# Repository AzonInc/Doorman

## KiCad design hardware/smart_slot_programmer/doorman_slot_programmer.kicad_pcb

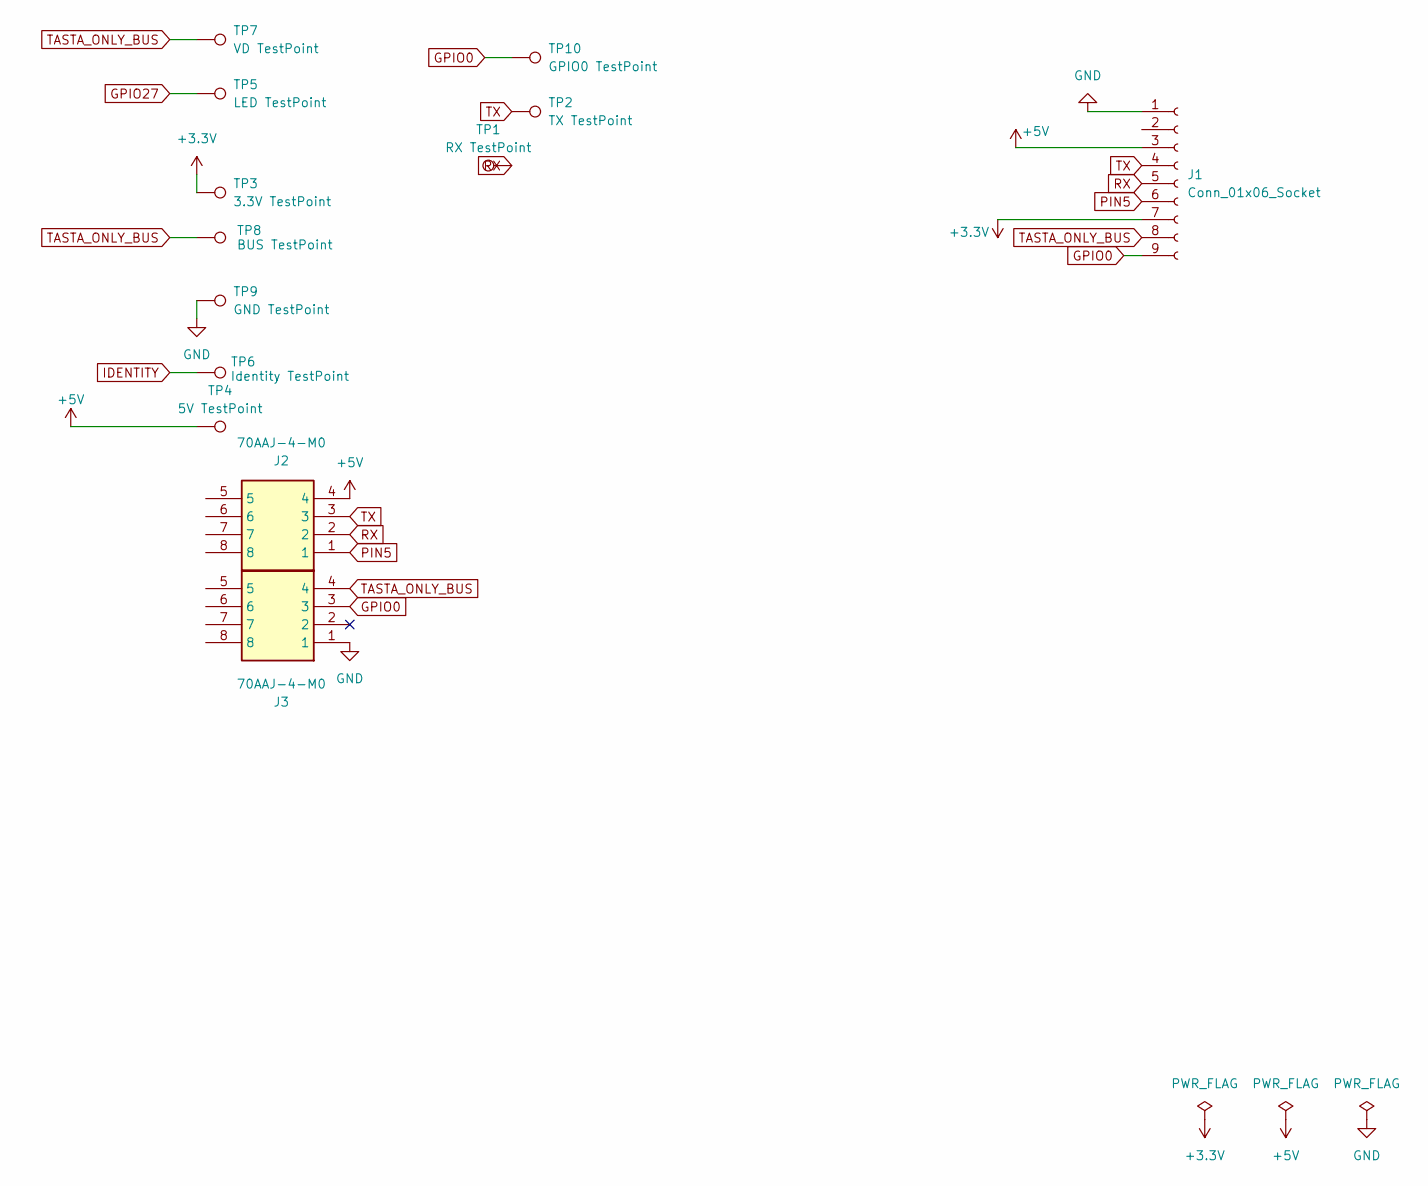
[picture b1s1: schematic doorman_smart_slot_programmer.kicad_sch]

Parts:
J1: Conn_01x06_Socket; PinSocket_1x09_P2.54mm_Horizontal
J2, J3: 70AAJ-4-M0; 70AAJ4M0; Manufacturer_Part_Number 70AAJ-4-M0; Mouser Part Number 652-70AAJ-4-M0
TP1: RX TestPoint; TestPoint_Pad_D1.0mm
TP2: TX TestPoint; TestPoint_Pad_D1.0mm
TP3: 3.3V TestPoint; TestPoint_Pad_D1.0mm
TP4: 5V TestPoint; TestPoint_Pad_D1.0mm
TP5: LED TestPoint; TestPoint_Pad_D1.0mm
TP6: Identity TestPoint; TestPoint_Pad_D1.0mm
TP7: VD TestPoint; TestPoint_Pad_D1.0mm
TP8: BUS TestPoint; TestPoint_Pad_D1.0mm
TP9: GND TestPoint; TestPoint_Pad_D1.0mm
TP10: GPIO0 TestPoint; TestPoint_Pad_D1.0mm

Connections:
+3.3V: J1.7, TP3.1
+5V: J1.3, J2.4, TP4.1
GND: J1.1, J3.1, TP9.1
GPIO0: J1.9, J3.3, TP10.1
GPIO27: TP5.1
IDENTITY: TP6.1
PIN5: J1.6, J2.1
RX: J1.5, J2.2, TP1.1
TASTA_ONLY_BUS: J1.8, J3.4, TP7.1, TP8.1
TX: J1.4, J2.3, TP2.1

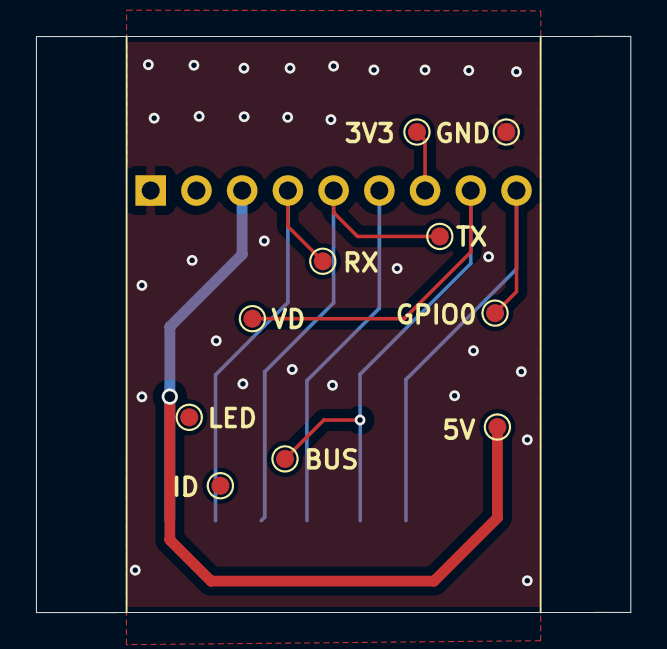
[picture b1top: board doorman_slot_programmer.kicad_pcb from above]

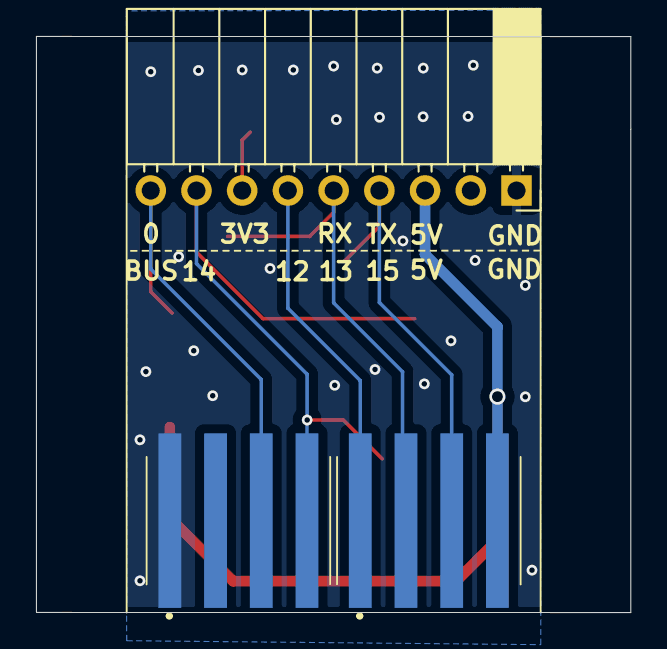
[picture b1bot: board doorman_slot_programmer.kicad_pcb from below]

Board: 4 copper layers, 33.0 x 32.0 mm, 13 parts (3 on the bottom side), 8 nets.

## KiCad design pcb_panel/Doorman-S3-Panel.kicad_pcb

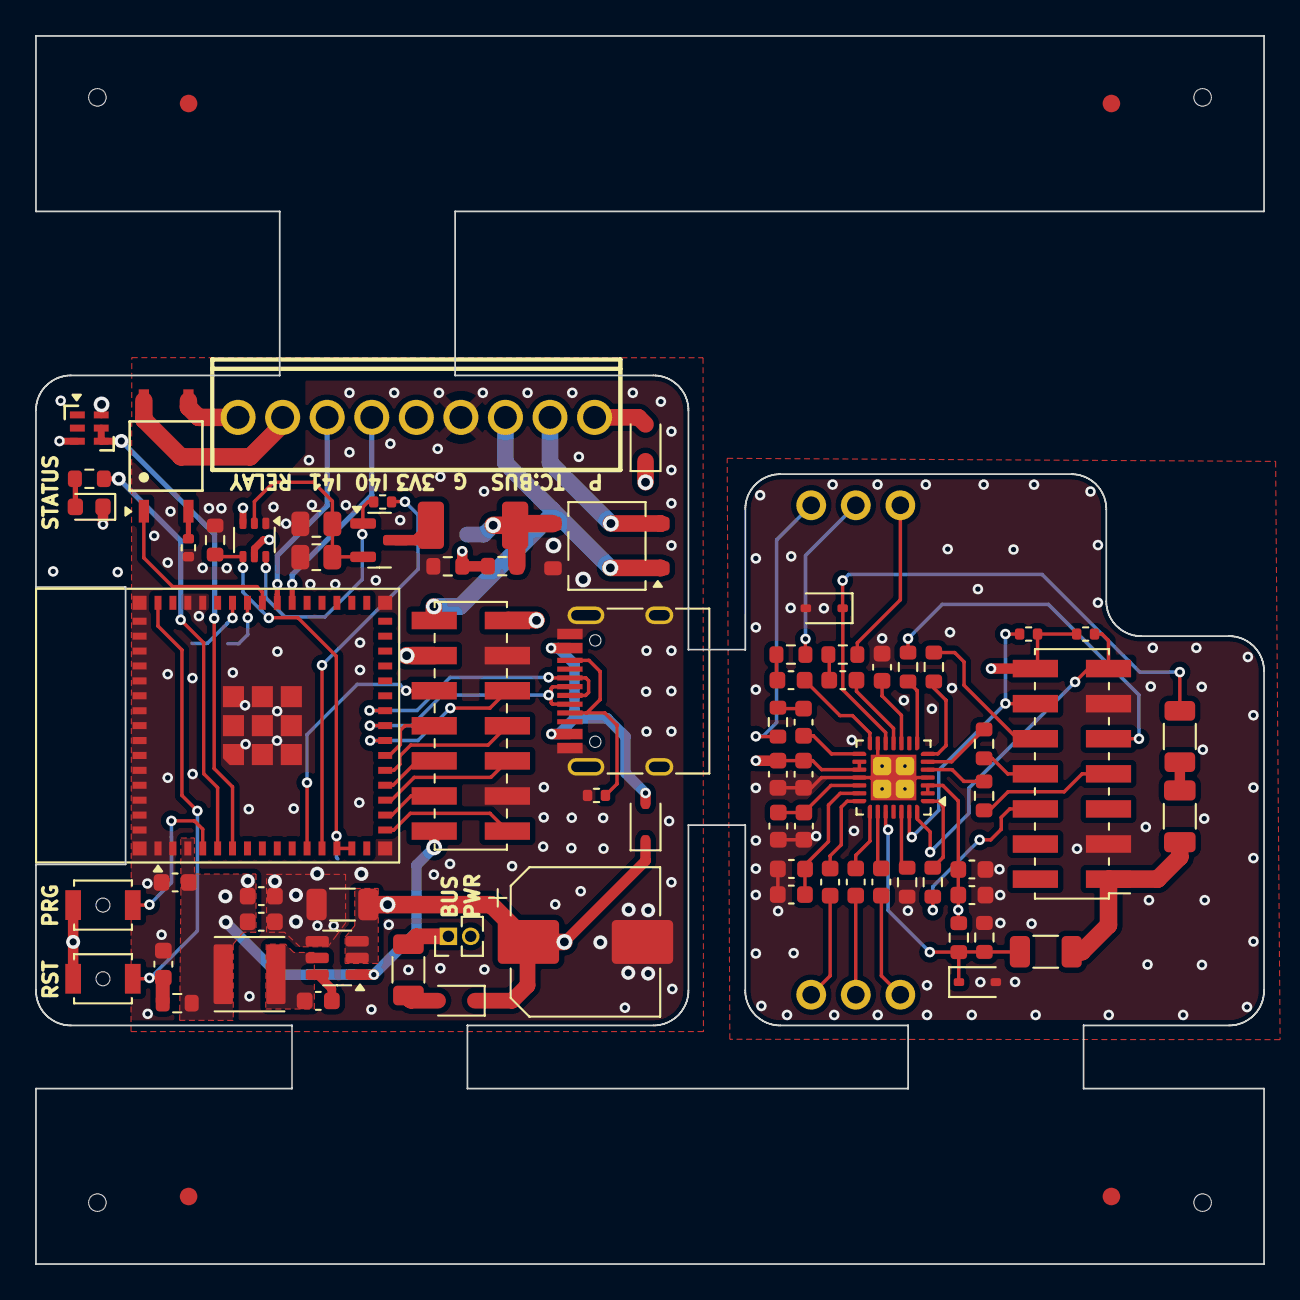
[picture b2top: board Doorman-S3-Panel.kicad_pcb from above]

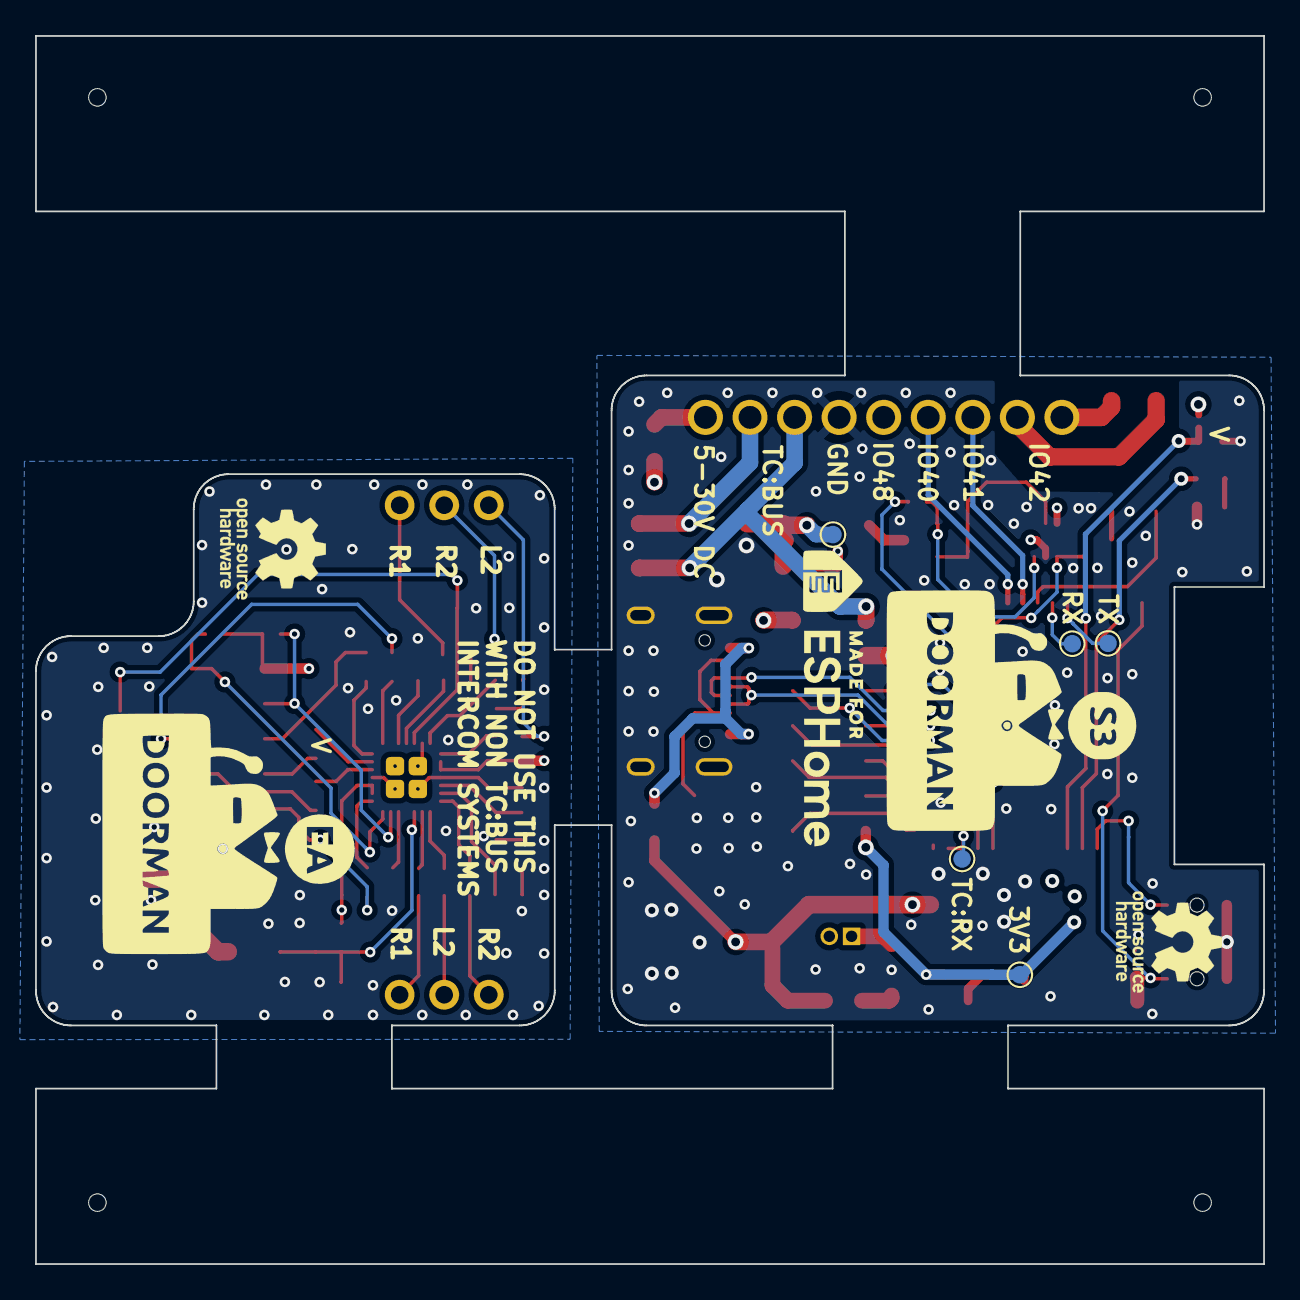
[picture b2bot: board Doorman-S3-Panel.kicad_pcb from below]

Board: 4 copper layers, 70.0 x 70.0 mm, 84 parts (12 on the bottom side), 79 nets.

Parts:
B0-C1, B0-C2, B0-C5, B1-C1, B1-C10, B1-C18, B1-C20: 100nF; C_0603_1608Metric
B0-C3: 470uF; CP_Elec_8x10
B0-C4: 10uF; C_1206_3216Metric
B0-C6, B0-C7: 22uF; C_0603_1608Metric
B0-D1, B0-D5, B0-D6: 1N5819WS; D_SOD-323
B0-D2: MB6S; TO-269AA
B0-D4: Red; LED_0603_1608Metric
B0-D7: 6.2V; D_MELF
B0-D8: XL-2020RGBC-SK6812B; LED-SMD_6P-L2.0-W2.0_XL-2020RGBC
B0-G***: LOGO; esphome
B0-G***#2, B1-G***: LOGO; doorman-s3-2
B0-J1: USB_C_Receptacle_USB2.0; USB_C_Receptacle_HRO_TYPE-C-31-M-12
B0-J2: Terminal; CONN-TH_9P-P2.54_KF128-2.54-9P
B0-J3: 3V3 Test Pad; TestPoint_Pad_D1.0mm
B0-J4: Conn_02x07_Odd_Even; PinSocket_2x07_P2.00mm_Vertical_SMD
B0-J6: BUS Test Pad; TestPoint_Pad_D1.0mm
B0-J7: BUS RX Test Pad; TestPoint_Pad_D1.0mm
B0-J8: TX Test Pad; TestPoint_Pad_D1.0mm
B0-J9: RX Test Pad; TestPoint_Pad_D1.0mm
B0-JP1: Bus power Jumper; PinHeader_1x02_P1.27mm_Vertical
B0-L1: 3.9uH; L_Abracon_ASPI-4030S
B0-Q1: BC847BPN; SOT-363_SC-70-6
B0-Q2: BC817; SOT-23
B0-R1, B0-R6, B0-R12, B1-R5, B1-R20, B1-R21: 10K; R_0603_1608Metric
B0-R2: 2.2K; R_0402_1005Metric
B0-R3: 5.1K; R_0402_1005Metric
B0-R5: 47K; R_0603_1608Metric
B0-R7: 470; R_0603_1608Metric
B0-R8, B0-R11: 1.2; R_0805_2012Metric
B0-R9: 150; R_0402_1005Metric
B0-R10: 62; R_1206_3216Metric
B0-REF**, B1-REF**: OSHW-Logo_5.7x6mm_SilkScreen
B0-SW1: Reset Button; SW_SPST_B3U-1000P-B
B0-SW2: Flash Button; SW_SPST_B3U-1000P-B
B0-U2: AP63203WU; TSOT-23-6
B0-U3: GAQY252G3S; SOP-4_L4.4-W4.0-P2.54-LS7.0-TL
B0-U4: ESP32-S3-MINI-1; ESP32-S2-MINI-1
B1-C2, B1-C11, B1-C17, B1-C19, B1-C21: 10uF; C_0603_1608Metric
B1-C3, B1-C4, B1-C5, B1-C6: 1uF; C_0603_1608Metric
B1-C7, B1-C13: 47uF; C_0603_1608Metric
B1-C12, B1-C14: 1uF; C_1206_3216Metric
B1-D1, B1-D2: CDSOD323-T03S; D_SOD-323
B1-J1: Audio Out; PinHeader_1x03_P2.54mm_Vertical
B1-J4: Extension Board Connector; PinHeader_2x07_P2.00mm_Vertical_SMD
B1-J5: Audio In; PinHeader_1x03_P2.54mm_Vertical
B1-R1, B1-R2, B1-R3: 10; R_0603_1608Metric
B1-R6: 1K; R_1206_3216Metric
B1-R13, B1-R14: 10K; R_0402_1005Metric
B1-R15, B1-R16, B1-R17, B1-R18, B1-R19: 33; R_0603_1608Metric
B1-U1: ES8388; QFN-28-1EP_4x4mm_P0.45mm_EP2.6x2.6mm

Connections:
B0-+3.3V: B0-C2.2, B0-C6.1, B0-C7.1, B0-D8.6 (VDD), B0-J2.5, B0-J3.1, B0-J4.2, B0-L1.2, B0-Q1.3 (C2), B0-R1.1, B0-U2.1 (FB), B0-U4.3 (3V3)
B0-+5V: B0-D1.2 (A), B0-J1.A4 (VBUS), B0-J1.A9 (VBUS), B0-J1.B4 (VBUS), B0-J1.B9 (VBUS)
B0-+24V Bus: B0-D2.3 (+), B0-D7.1 (K), B0-J6.1, B0-JP1.2 (B), B0-R5.2
B0-/EN: B0-C1.1, B0-R1.2, B0-SW1.1, B0-U4.45 (EN)
B0-/FLASH: B0-SW2.1, B0-U4.4 (IO0)
B0-/RXD: B0-J9.1, B0-U4.40 (RXD0)
B0-/TXD: B0-J8.1, B0-U4.39 (TXD0)
B0-/VCC_IN: B0-C3.1, B0-C4.1, B0-D1.1 (K), B0-D5.1 (K), B0-D6.1 (K), B0-J4.12, B0-U2.2 (EN), B0-U2.3 (IN)
B0-BUS_CONN: B0-J7.1, B0-Q1.4 (E2), B0-R12.1, B0-U4.13 (IO9), B0-U4.14 (IO10)
B0-BUS_TX: B0-R2.1, B0-U4.12 (IO8)
B0-BUS_WIRE1: B0-D2.1, B0-J2.3, B0-J4.14
B0-BUS_WIRE2: B0-D2.2, B0-J2.2, B0-J4.13
B0-GND: B0-C1.2, B0-C2.1, B0-C3.2, B0-C4.2, B0-C6.2, B0-C7.2, B0-D2.4 (-), B0-D4.1 (K), B0-D8.3 (GND), B0-J1.A1 (GND), B0-J1.A12 (GND), B0-J1.B1 (GND), B0-J1.B12 (GND), B0-J1.S1 (SHIELD), B0-J2.4, B0-J4.3, B0-J4.11, B0-Q1.1 (E1), B0-R3.2, B0-R6.2, B0-R8.2, B0-R9.2, B0-R11.2, B0-R12.2, B0-SW1.2, B0-SW2.2, B0-U2.4 (GND), B0-U4.1 (GND), B0-U4.2 (GND), B0-U4.42 (GND), B0-U4.43 (GND), B0-U4.46 (GND), B0-U4.47 (GND), B0-U4.48 (GND), B0-U4.49 (GND), B0-U4.50 (GND), B0-U4.51 (GND), B0-U4.52 (GND), B0-U4.53 (GND), B0-U4.54 (GND), B0-U4.55 (GND), B0-U4.56 (GND), B0-U4.57 (GND), B0-U4.58 (GND), B0-U4.59 (GND), B0-U4.60 (GND), B0-U4.61 (GND), B0-U4.62 (GND), B0-U4.63 (GND), B0-U4.64 (GND), B0-U4.65 (GND)
B0-I2C_CLK: B0-J4.1, B0-U4.16 (IO12)
B0-I2C_DAT: B0-J4.4, B0-U4.17 (IO13)
B0-IO7: B0-J4.10, B0-U4.11 (IO7)
B0-IO14: B0-J4.5, B0-U4.18 (IO14)
B0-IO15: B0-J4.6, B0-U4.19 (IO15)
B0-IO16: B0-J4.7, B0-U4.20 (IO16)
B0-IO17: B0-J4.8, B0-U4.21 (IO17)
B0-IO18: B0-J4.9, B0-U4.22 (IO18)
B0-IO40: B0-J2.6, B0-U4.36 (IO40)
B0-IO41: B0-J2.7, B0-U4.37 (IO41)
B0-LED_RED: B0-R7.1, B0-U4.5 (IO1)
B0-LED_RGB: B0-D8.4 (DI2), B0-D8.5 (DI1), B0-U4.6 (IO2)
B0-Net-(D4-A): B0-D4.2 (A), B0-R7.2
B0-Net-(D6-A): B0-D6.2 (A), B0-R10.1
B0-Net-(D7-A): B0-D7.2 (A), B0-Q2.3 (C)
B0-Net-(J1-CC1): B0-J1.A5 (CC1), B0-J1.B5 (CC2), B0-R3.1
B0-Net-(JP1-A): B0-JP1.1 (A), B0-R10.2
B0-Net-(Q1A-B1): B0-Q1.2 (B1), B0-Q2.2 (E), B0-R8.1, B0-R11.1
B0-Net-(Q1A-C1): B0-Q1.6 (C1), B0-Q2.1 (B), B0-R2.2
B0-Net-(Q1B-B2): B0-Q1.5 (B2), B0-R5.1, B0-R6.1
B0-Net-(R9-Pad1): B0-R9.1, B0-U3.2
B0-Net-(U2-BST): B0-C5.1, B0-U2.6 (BST)
B0-Net-(U2-SW): B0-C5.2, B0-L1.1, B0-U2.5 (SW)
B0-RELAY_WIRE1: B0-J2.9, B0-U3.3
B0-RELAY_WIRE2: B0-J2.8, B0-U3.4
B0-SSR: B0-U3.1, B0-U4.38 (IO42)
B0-USB_D+: B0-J1.A6 (D+), B0-J1.B6 (D+), B0-U4.24 (USB_D+)
B0-USB_D-: B0-J1.A7 (D-), B0-J1.B7 (D-), B0-U4.23 (USB_D-)
B0-VCC: B0-D5.2 (A), B0-J2.1
B1-+3.3V: B1-C1.2, B1-C2.2, B1-C10.2, B1-C11.2, B1-J4.14, B1-R13.1, B1-R14.1, B1-R20.1, B1-U1.2 (DVDD), B1-U1.3 (PVDD), B1-U1.16 (HPVDD), B1-U1.17 (AVDD)
B1-AUDIO_IN_L1: B1-C12.2, B1-D1.1 (K), B1-R20.2, B1-R21.1, B1-U1.24 (LIN1)
B1-AUDIO_IN_L2: B1-C5.2, B1-J5.2
B1-AUDIO_IN_R1: B1-C4.2, B1-J5.3
B1-AUDIO_IN_R2: B1-C3.2, B1-J5.1
B1-AUDIO_OUT_L1: B1-D2.1 (K), B1-R6.1, B1-U1.12 (LOUT1)
B1-AUDIO_OUT_L2: B1-J1.1, B1-R2.2
B1-AUDIO_OUT_R1: B1-J1.3, B1-R1.2
B1-AUDIO_OUT_R2: B1-J1.2, B1-R3.2
B1-BUS_WIRE2: B1-C12.1, B1-C14.1, B1-J4.1
B1-GND: B1-C1.1, B1-C2.1, B1-C10.1, B1-C11.1, B1-C17.1, B1-C18.1, B1-C19.1, B1-C20.1, B1-C21.1, B1-D1.2 (A), B1-D2.2 (A), B1-J4.3, B1-J4.11, B1-R5.1, B1-R21.2, B1-U1.4 (DGND), B1-U1.13 (HPGND), B1-U1.18 (AGND), B1-U1.29 (EPAD)
B1-I2C_CLK: B1-J4.13, B1-R14.2, B1-U1.28 (CCLK)
B1-I2C_DAT: B1-J4.12, B1-R13.2, B1-U1.27 (CDATA)
B1-I2S_DAT_IN: B1-J4.8, B1-R18.2
B1-I2S_DAT_OUT: B1-J4.9, B1-R19.2
B1-I2S_LRCK: B1-J4.10, B1-R17.2
B1-I2S_MCLK: B1-J4.6, B1-R15.2
B1-I2S_SCLK: B1-J4.7, B1-R16.2
B1-Net-(C6-Pad2): B1-C6.2, B1-R1.1
B1-Net-(C7-Pad2): B1-C7.2, B1-R2.1
B1-Net-(C13-Pad2): B1-C13.2, B1-R3.1
B1-Net-(C14-Pad2): B1-C14.2, B1-R6.2
B1-Net-(U1-ADCVREF): B1-C18.2, B1-C19.2, B1-U1.19 (ADCVREF)
B1-Net-(U1-ASDOUT): B1-R19.1, B1-U1.8 (ASDOUT)
B1-Net-(U1-CE): B1-R5.2, B1-U1.26 (CE)
B1-Net-(U1-DSDIN): B1-R18.1, B1-U1.6 (DSDIN)
B1-Net-(U1-LIN2): B1-C5.1, B1-U1.22 (LIN2)
B1-Net-(U1-LOUT2): B1-C7.1, B1-U1.15 (LOUT2)
B1-Net-(U1-LRCK): B1-R17.1, B1-U1.7 (LRCK)
B1-Net-(U1-MCLK): B1-R15.1, B1-U1.1 (MCLK)
B1-Net-(U1-RIN1): B1-C4.1, B1-U1.23 (RIN1)
B1-Net-(U1-RIN2): B1-C3.1, B1-U1.21 (RIN2)
B1-Net-(U1-ROUT1): B1-C6.1, B1-U1.11 (ROUT1)
B1-Net-(U1-ROUT2): B1-C13.1, B1-U1.14 (ROUT2)
B1-Net-(U1-SCLK): B1-R16.1, B1-U1.5 (SCLK)
B1-Net-(U1-VMID): B1-C20.2, B1-C21.2, B1-U1.20 (VMID)
B1-Net-(U1-VREF): B1-C17.2, B1-U1.10 (VREF)

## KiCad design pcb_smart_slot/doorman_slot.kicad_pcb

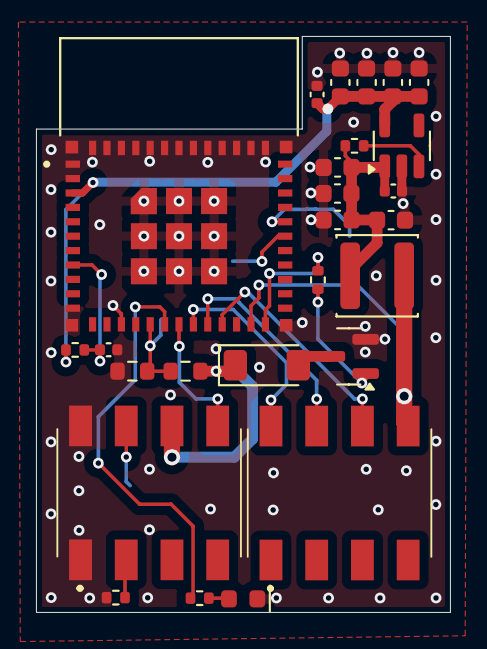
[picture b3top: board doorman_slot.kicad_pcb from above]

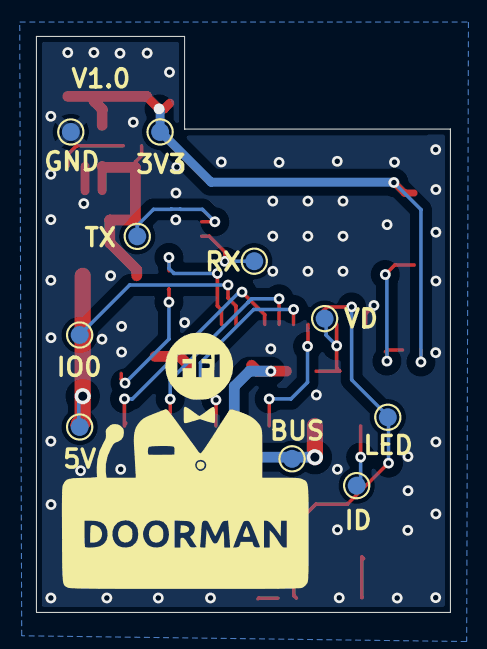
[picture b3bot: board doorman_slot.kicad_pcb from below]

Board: 4 copper layers, 23.0 x 32.0 mm, 36 parts (10 on the bottom side), 22 nets.

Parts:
C1, C2, C3, C4, C6, C7, C8, C9: 22uF; C_0603_1608Metric
C5, C11: 100nF; C_0402_1005Metric
C10: 22uF; C_0402_1005Metric
D1: Red LED; LED_0603_1608Metric
D2: 6V2; D_MiniMELF
J2, J3: 70AAJ-4-M0; 70AAJ4M0
L1: 22uH; L_APV_ANR4010
Q1: BC817; SOT-23
R1: 2.2K; R_0402_1005Metric
R3, R5: 10K; R_0402_1005Metric
R6: 402; R_0402_1005Metric
R7: 1M; R_0603_1608Metric
R8: 160K; R_0603_1608Metric
R9: 1K; R_0402_1005Metric
TP1: RX TestPoint; TestPoint_Pad_D1.0mm
TP2: TX TestPoint; TestPoint_Pad_D1.0mm
TP3: 3.3V TestPoint; TestPoint_Pad_D1.0mm
TP4: 5V TestPoint; TestPoint_Pad_D1.0mm
TP5: LED TestPoint; TestPoint_Pad_D1.0mm
TP6: Identity TestPoint; TestPoint_Pad_D1.0mm
TP7: VD TestPoint; TestPoint_Pad_D1.0mm
TP8: BUS TestPoint; TestPoint_Pad_D1.0mm
TP9: GND TestPoint; TestPoint_Pad_D1.0mm
TP10: GPIO0 TestPoint; TestPoint_Pad_D1.0mm
U2: XC6210B332MR; SOT-23-5
U3: ESP32-PICO-MINI-02; MODULE_ESP32-PICO-MINI-02

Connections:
+3.3V: C6.1, C7.1, C8.1, C9.1, C10.1, R5.1, TP3.1, U2.5 (VOUT), U3.3 (3V3)
+5V: J3.5, L1.1, TP4.1
GND: C1.1, C2.2, C3.2, C4.2, C5.1, C6.2, C7.2, C8.2, C9.2, C10.2, C11.1, D1.1 (K), J2.1, J2.8, Q1.2 (E), R1.1, R8.1, TP9.1, U2.2 (GND), U3.1 (GND), U3.2 (GND), U3.11 (GND), U3.14 (GND), U3.36 (GND), U3.37 (GND), U3.38 (GND), U3.39 (GND), U3.40 (GND), U3.41 (GND), U3.42 (GND), U3.43 (GND), U3.44 (GND), U3.45 (GND), U3.46 (GND), U3.47 (GND), U3.48 (GND), U3.49 (GND), U3.50 (GND), U3.51 (GND), U3.52 (GND), U3.53 (GND), U3.54 (GND), U3.55 (GND), U3.56 (GND), U3.57 (GND), U3.58 (GND), U3.59 (GND), U3.60 (GND), U3.61 (GND)
GPIO0: TP10.1, U3.23 (IO0)
GPIO4: R9.1, U3.24 (IO4)
GPIO12: J3.8, U3.19 (IO12)
GPIO13: J3.7, U3.20 (IO13)
GPIO14: J2.5, U3.18 (IO14)
GPIO15: J3.6, U3.21 (IO15)
GPIO26: R7.2, R8.2, TP7.1, U3.16 (IO26)
GPIO27: R6.2, TP5.1, U3.17 (IO27)
IDENTITY: J2.2, R1.2
unnamed: D1.2 (A), R6.1
unnamed: D2.2 (A), Q1.3 (C)
unnamed: J2.7, TP6.1
unnamed: Q1.1 (B), R9.2
unnamed: R3.2, U2.3 (CE)
unnamed: C1.2, C2.1, C3.1, C4.1, C5.2, L1.2, R3.1, U2.1 (VIN)
unnamed: C11.2, R5.2, U3.8 (EN)
RX: TP2.1, U3.30 (RXD0)
TASTA_ONLY_BUS: D2.1 (K), J2.6, R7.1, TP8.1
TX: TP1.1, U3.31 (TXD0)
